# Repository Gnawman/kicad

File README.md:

# kicad

## Getting started

To make it easy for you to get started with GitLab, here's a list of recommended next steps.

Already a pro? Just edit this README.md and make it your own. Want to make it easy? [Use the template at the bottom](#editing-this-readme)!

## Add your files

- [ ] [Create](https://docs.gitlab.com/ee/user/project/repository/web_editor.html#create-a-file) or [upload](https://docs.gitlab.com/ee/user/project/repository/web_editor.html#upload-a-file) files
- [ ] [Add files using the command line](https://docs.gitlab.com/ee/gitlab-basics/add-file.html#add-a-file-using-the-command-line) or push an existing Git repository with the following command:

```
cd existing_repo
git remote add origin https://gitlab.com/gnawman/kicad.git
git branch -M main
git push -uf origin main
```

## Integrate with your tools

- [ ] [Set up project integrations](https://gitlab.com/gnawman/kicad/-/settings/integrations)

## Collaborate with your team

- [ ] [Invite team members and collaborators](https://docs.gitlab.com/ee/user/project/members/)
- [ ] [Create a new merge request](https://docs.gitlab.com/ee/user/project/merge_requests/creating_merge_requests.html)
- [ ] [Automatically close issues from merge requests](https://docs.gitlab.com/ee/user/project/issues/managing_issues.html#closing-issues-automatically)
- [ ] [Enable merge request approvals](https://docs.gitlab.com/ee/user/project/merge_requests/approvals/)
- [ ] [Automatically merge when pipeline succeeds](https://docs.gitlab.com/ee/user/project/merge_requests/merge_when_pipeline_succeeds.html)

## Test and Deploy

Use the built-in continuous integration in GitLab.

- [ ] [Get started with GitLab CI/CD](https://docs.gitlab.com/ee/ci/quick_start/index.html)
- [ ] [Analyze your code for known vulnerabilities with Static Application Security Testing(SAST)](https://docs.gitlab.com/ee/user/application_security/sast/)
- [ ] [Deploy to Kubernetes, Amazon EC2, or Amazon ECS using Auto Deploy](https://docs.gitlab.com/ee/topics/autodevops/requirements.html)
- [ ] [Use pull-based deployments for improved Kubernetes management](https://docs.gitlab.com/ee/user/clusters/agent/)
- [ ] [Set up protected environments](https://docs.gitlab.com/ee/ci/environments/protected_environments.html)

***

# Editing this README

When you're ready to make this README your own, just edit this file and use the handy template below (or feel free to structure it however you want - this is just a starting point!). Thank you to [makeareadme.com](https://www.makeareadme.com/) for this template.

## Suggestions for a good README
Every project is different, so consider which of these sections apply to yours. The sections used in the template are suggestions for most open source projects. Also keep in mind that while a README can be too long and detailed, too long is better than too short. If you think your README is too long, consider utilizing another form of documentation rather than cutting out information.

## Name
Choose a self-explaining name for your project.

## Description
Let people know what your project can do specifically. Provide context and add a link to any reference visitors might be unfamiliar with. A list of Features or a Background subsection can also be added here. If there are alternatives to your project, this is a good place to list differentiating factors.

## Badges
On some READMEs, you may see small images that convey metadata, such as whether or not all the tests are passing for the project. You can use Shields to add some to your README. Many services also have instructions for adding a badge.

## Visuals
Depending on what you are making, it can be a good idea to include screenshots or even a video (you'll frequently see GIFs rather than actual videos). Tools like ttygif can help, but check out Asciinema for a more sophisticated method.

## Installation
Within a particular ecosystem, there may be a common way of installing things, such as using Yarn, NuGet, or Homebrew. However, consider the possibility that whoever is reading your README is a novice and would like more guidance. Listing specific steps helps remove ambiguity and gets people to using your project as quickly as possible. If it only runs in a specific context like a particular programming language version or operating system or has dependencies that have to be installed manually, also add a Requirements subsection.

## Usage
Use examples liberally, and show the expected output if you can. It's helpful to have inline the smallest example of usage that you can demonstrate, while providing links to more sophisticated examples if they are too long to reasonably include in the README.

## Support
Tell people where they can go to for help. It can be any combination of an issue tracker, a chat room, an email address, etc.

## Roadmap
If you have ideas for releases in the future, it is a good idea to list them in the README.

## Contributing
State if you are open to contributions and what your requirements are for accepting them.

For people who want to make changes to your project, it's helpful to have some documentation on how to get started. Perhaps there is a script that they should run or some environment variables that they need to set. Make these steps explicit. These instructions could also be useful to your future self.

You can also document commands to lint the code or run tests. These steps help to ensure high code quality and reduce the likelihood that the changes inadvertently break something. Having instructions for running tests is especially helpful if it requires external setup, such as starting a Selenium server for testing in a browser.

## Authors and acknowledgment
Show your appreciation to those who have contributed to the project.

## License
For open source projects, say how it is licensed.

## Project status
If you have run out of energy or time for your project, put a note at the top of the README saying that development has slowed down or stopped completely. Someone may choose to fork your project or volunteer to step in as a maintainer or owner, allowing your project to keep going. You can also make an explicit request for maintainers.

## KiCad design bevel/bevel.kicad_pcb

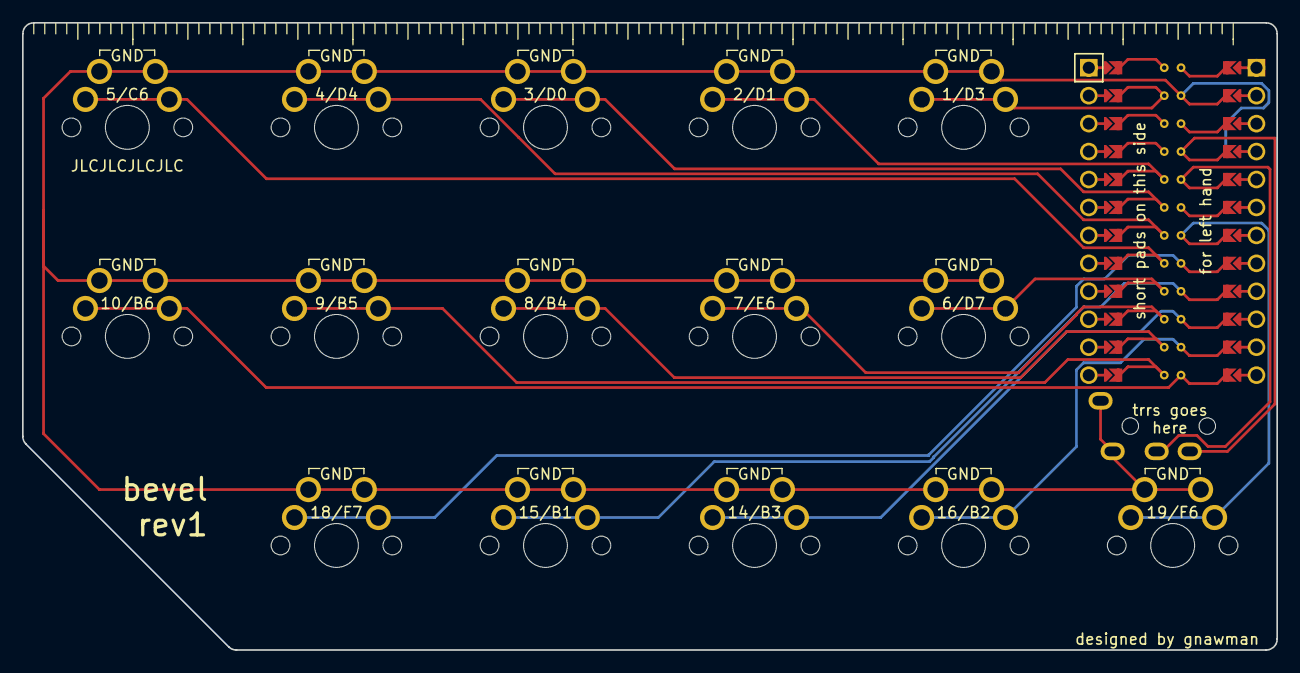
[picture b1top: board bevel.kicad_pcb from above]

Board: 2 copper layers, 114.0 x 57.0 mm, 16 parts (0 on the bottom side), 16 nets.

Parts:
MCU1: ProMicro
S1, S2, S3, S4, S5, S6, S7, S8, S9, S10, S11, S12, S13, S14, S15: MX

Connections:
GND: MCU1.2, MCU1.21, MCU1.22, S1.1, S2.1, S3.1, S4.1, S5.1, S6.1, S7.1, S8.1, S9.1, S10.1, S11.1, S12.1, S13.1, S14.1, S15.1
matrix_inner_bottom: MCU1.7, S13.2
matrix_inner_home: MCU1.16, S14.2
matrix_inner_top: MCU1.23, S15.2
matrix_middle_bottom: MCU1.10, S7.2
matrix_middle_home: MCU1.14, S8.2
matrix_middle_top: MCU1.19, S9.2
matrix_pinky_bottom: MCU1.8, S1.2
matrix_pinky_home: MCU1.12, S2.2
matrix_pinky_top: MCU1.17, S3.2
matrix_pointer_bottom: MCU1.11, S10.2
matrix_pointer_home: MCU1.15, S11.2
matrix_pointer_top: MCU1.20, S12.2
matrix_ring_bottom: MCU1.9, S4.2
matrix_ring_home: MCU1.13, S5.2
matrix_ring_top: MCU1.18, S6.2

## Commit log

2023-04-14 readme: deleted readme
2023-04-14 housekeeping: moved some gerbers around so file structure is uniform
2023-04-14 erjo45: moved folders around to match the folder structure of the rest of the keebs
2023-04-15 erjo45: rev4 is just about up to scratch
2023-05-06 finally settled on a name - shingleback! changed rj45 port to reflect reality
2023-05-06 don't know what this change was, hopefully it's just kicad weirdness
2023-05-21 final rev1 commit before manufacturing
2023-06-05 shingleback rev2
2023-06-05 updated project local settings
2023-06-05 formatting readme, how into markdown
2023-06-05 added render of shingleback
2023-06-06 changed net names to reflect reality
2023-06-06 ensuring expansion slot can be used for I2C communication
2023-06-19 projects re-organised, library created and included in repo
2023-06-19 updated url for pic
2023-06-19 kicad auto-backup
2023-06-19 momentary button footprint
2023-06-19 completed rev1
2023-06-19 autogenerated backups
2023-06-19 renamed to thorny devil
2023-06-21 final rev1 commit before manufacture
2023-09-30 added mx\gateron-lowpro hybrid footprint
2023-09-30 setup for shingleback rev3
2023-09-30 split off skink into separate keb
2023-09-30 skink initial commit
2024-01-02 rev2
